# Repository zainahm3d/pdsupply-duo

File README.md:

# pdsupply-duo
2 channel USB PD power supply

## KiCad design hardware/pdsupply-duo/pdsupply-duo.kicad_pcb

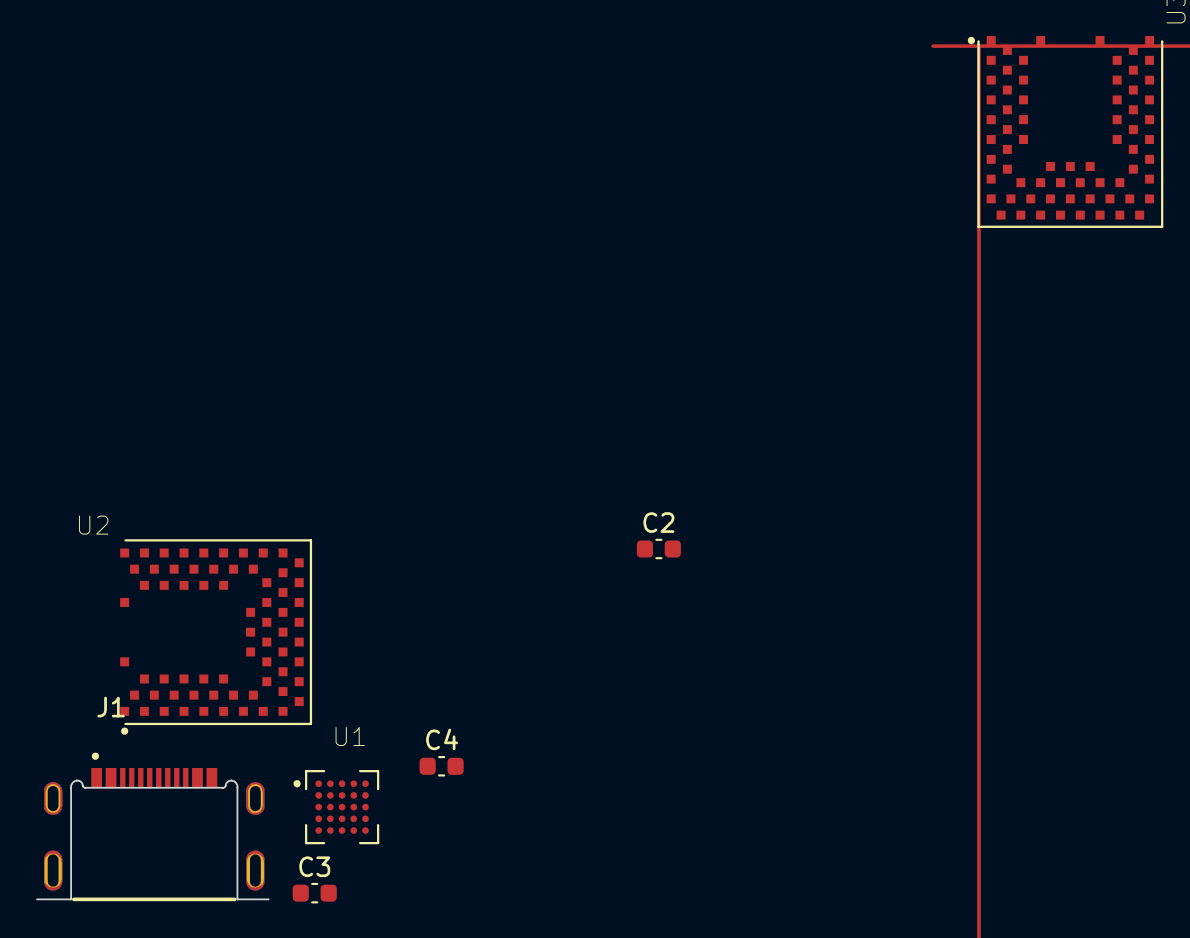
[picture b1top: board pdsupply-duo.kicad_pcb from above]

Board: 2 copper layers, 7 parts (0 on the bottom side), 6 nets, no tracks yet.

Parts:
C2, C3: .1uF; C_0603_1608Metric
C4: 4.7uF; C_0603_1608Metric
J1: USB4505-03-0-A_REVA; GCT_USB4505-03-0-A_REVA
U1: LTM8074IY; BGA25C65P5X5_400X400X198N
U2, U3: BMD-340-A-R; RIGADO_BMD-340-A-R

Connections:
+3V3: C2.1, C3.1, C4.1, U1.E1 (VOUT), U1.E2 (VOUT), U2.17 (VCC1), U2.65 (VCCH1)
GND: C2.2, C3.2, C4.2, J1.A1_B12 (GND_A), J1.B1_A12 (GND_B), J1.S1 (SHELL_GND), J1.S2 (SHELL_GND), J1.S3 (SHELL_GND), J1.S4 (SHELL_GND), U1.A1 (GND), U1.A5 (GND), U1.B2 (GND), U1.B3 (GND), U1.B4 (GND), U1.C2 (GND), U1.C3 (GND), U1.C4 (GND), U1.C5 (GND), U1.D2 (GND), U1.D3 (GND), U1.D4 (GND), U1.D5 (SYNC), U1.E3 (GND), U1.E4 (GND), U1.E5 (GND), U2.1 (GND), U2.2 (GND), U2.3 (GND), U2.4 (GND), U2.5 (GND), U2.16 (GND), U2.18 (GND), U2.29 (GND), U2.30 (GND), U2.45 (GND), U2.46 (GND), U2.47 (GND), U2.55 (GND)
unnamed: J1.A6 (DP1), J1.B6 (DP2)
unnamed: J1.A7 (DN1), J1.B7 (DN2)
unnamed: U3.1 (GND), U3.2 (GND), U3.3 (GND), U3.4 (GND), U3.5 (GND), U3.16 (GND), U3.18 (GND), U3.29 (GND), U3.30 (GND), U3.45 (GND), U3.46 (GND), U3.47 (GND), U3.55 (GND)
VBUS: J1.A4_B9 (VBUS_A), J1.B4_A9 (VBUS_B), U1.A2 (RUN), U1.A3 (VIN), U1.A4 (VIN)

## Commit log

2022-03-05 init
2022-03-05 add stm32 fw build folder to gitignore
2022-03-06 Added few more parts to comp folder
2022-03-13 Added Power for digital hardware
2022-03-16 added a LTspice sim, for testing
2022-04-03 Added usb PD interface
2022-04-08 SCH 85% done
